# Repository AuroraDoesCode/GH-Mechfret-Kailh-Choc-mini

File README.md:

# GH-Mechfret-Kailh-Choc-mini with LEDs!!!
Custom drop-in replacement for the fret PCB for Guitar Hero controllers using Kailh Choc Mini switches. Please check the license before use.

This should fit all guitars, except the WoR guitar. A separate board will be released for this guitar, supporting Choc V1's.

LEDs are SK9822-ec20. Choc Mini Variants require you to trim a small amount of plastic where the LED sits below the button. Its not awful to do, it takes two snips. Just be careful to not cut the sidewall of the button, or the LED will bleed to the next one.

Choc Mini board is tested and works as expected, Choc V1/V2 is currently untested, waiting for my dev boards.

Version 2 is now available, featuring support for both Choc V1/V2's, with SK9822-EC20 Suport.

To produce either of these boards, you can use the files in the {variant}/production folder on JLCPCB. Both can be produced either with or without LED's.

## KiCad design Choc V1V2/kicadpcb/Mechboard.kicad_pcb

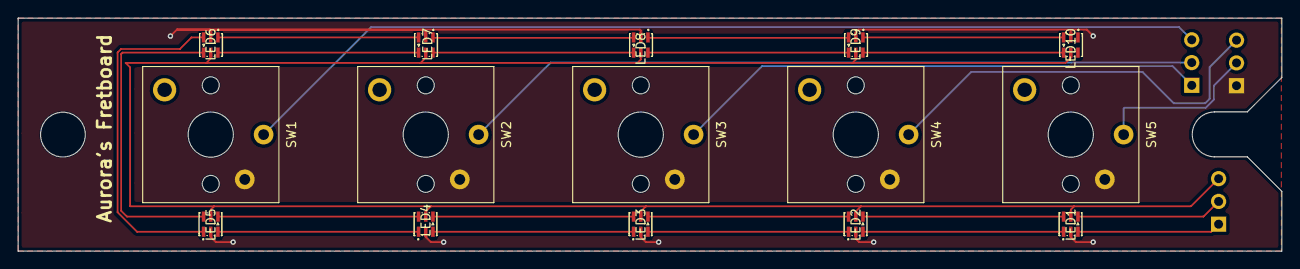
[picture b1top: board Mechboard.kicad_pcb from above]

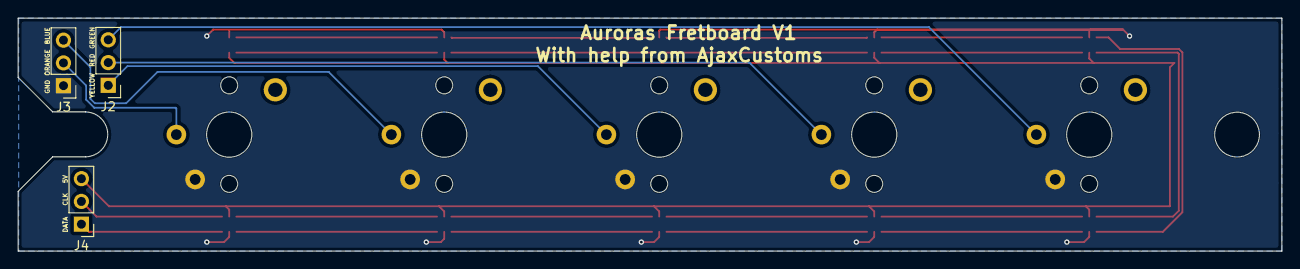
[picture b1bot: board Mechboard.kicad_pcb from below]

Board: 2 copper layers, 141.1 x 26.0 mm, 18 parts (3 on the bottom side), 27 nets.

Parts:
J2, J3, J4: Conn_01x03_Pin; PinHeader_1x03_P2.54mm_Vertical
LED1, LED2, LED3, LED4, LED5, LED6, LED7, LED8, LED9, LED10: SK9822-EC20
SW1, SW2, SW3, SW4, SW5: SW_Push; SW_Kailh_Choc_V1V2

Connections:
GND: J3.1, LED1.2 (GND), LED2.2 (GND), LED3.2 (GND), LED4.2 (GND), LED5.2 (GND), LED6.2 (GND), LED7.2 (GND), LED8.2 (GND), LED9.2 (GND), LED10.2 (GND), SW1.2, SW2.2, SW3.2, SW4.2, SW5.2
unnamed: J2.1, SW3.1
unnamed: J2.2, SW2.1
unnamed: J2.3, SW1.1
unnamed: J3.2, SW5.1
unnamed: J3.3, SW4.1
unnamed: J4.1, LED1.3 (SDI)
unnamed: J4.2, LED1.4 (CKI)
unnamed: J4.3, LED1.5 (VDD), LED2.5 (VDD), LED3.5 (VDD), LED4.5 (VDD), LED5.5 (VDD), LED6.5 (VDD), LED7.5 (VDD), LED8.5 (VDD), LED9.5 (VDD), LED10.5 (VDD)
unnamed: LED1.6 (CKO), LED2.4 (CKI)
unnamed: LED1.1 (SDO), LED2.3 (SDI)
unnamed: LED2.6 (CKO), LED3.4 (CKI)
unnamed: LED2.1 (SDO), LED3.3 (SDI)
unnamed: LED3.6 (CKO), LED4.4 (CKI)
unnamed: LED3.1 (SDO), LED4.3 (SDI)
unnamed: LED4.6 (CKO), LED5.4 (CKI)
unnamed: LED4.1 (SDO), LED5.3 (SDI)
unnamed: LED5.6 (CKO), LED6.4 (CKI)
unnamed: LED5.1 (SDO), LED6.3 (SDI)
unnamed: LED6.6 (CKO), LED7.4 (CKI)
unnamed: LED6.1 (SDO), LED7.3 (SDI)
unnamed: LED7.6 (CKO), LED8.4 (CKI)
unnamed: LED7.1 (SDO), LED8.3 (SDI)
unnamed: LED8.6 (CKO), LED9.4 (CKI)
unnamed: LED8.1 (SDO), LED9.3 (SDI)
unnamed: LED9.6 (CKO), LED10.4 (CKI)
unnamed: LED9.1 (SDO), LED10.3 (SDI)

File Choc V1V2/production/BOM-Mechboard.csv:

Comment,Designator,Footprint,LCSC,Quantity
~,"LED1,LED10,LED2,LED3,LED4,LED5,LED6,LED7,LED8,LED9",SK9822-EC20,C2909059,10
Conn_01x03_Pin,J2,PinHeader_1x03_P2.54mm_Vertical,,1
Conn_01x03_Pin,J3,PinHeader_1x03_P2.54mm_Vertical,,1
Conn_01x03_Pin,J4,PinHeader_1x03_P2.54mm_Vertical,,1
SW_Push,SW1,SW_Kailh_Choc_V1V2,,1
SW_Push,SW2,SW_Kailh_Choc_V1V2,,1
SW_Push,SW3,SW_Kailh_Choc_V1V2,,1
SW_Push,SW4,SW_Kailh_Choc_V1V2,,1
SW_Push,SW5,SW_Kailh_Choc_V1V2,,1
